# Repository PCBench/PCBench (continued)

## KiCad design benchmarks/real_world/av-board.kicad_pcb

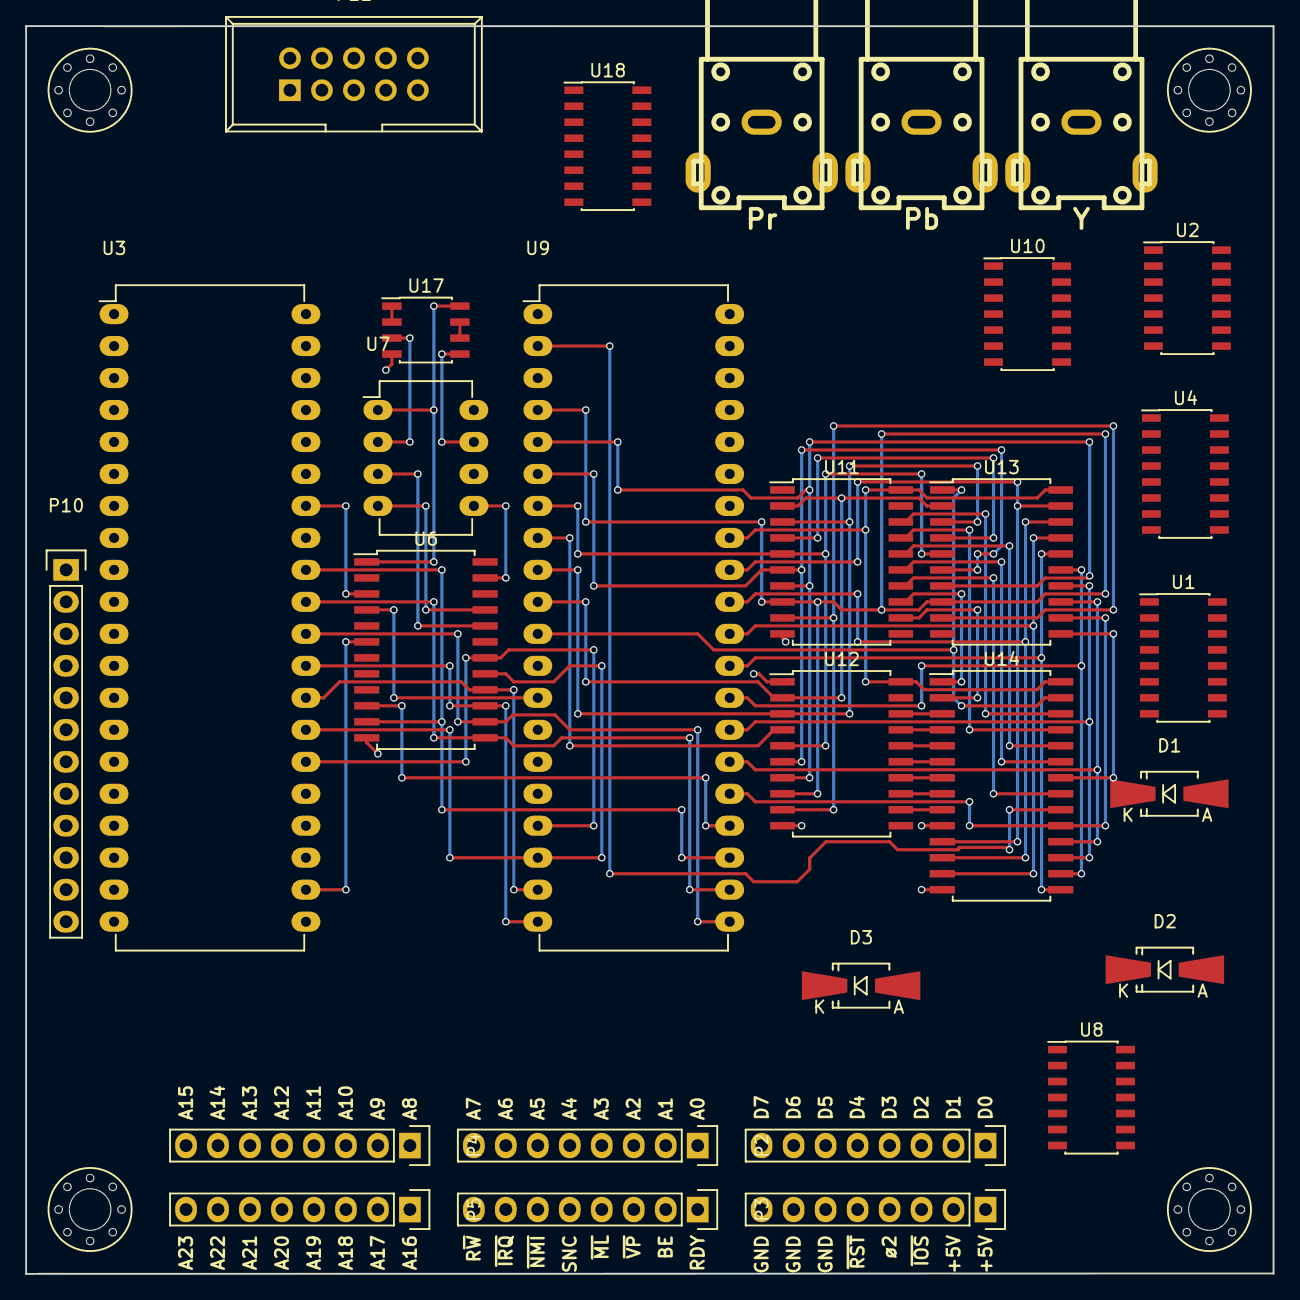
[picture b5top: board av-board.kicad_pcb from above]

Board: 2 copper layers, 99.1 x 99.1 mm, 33 parts (0 on the bottom side), 92 nets.

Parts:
D1, D2, D3: D_Small; SMA-SMB_Universal_Handsoldering
P1: D0..D7; Pin_Header_Straight_1x08
P2: A0..A7; Pin_Header_Straight_1x08
P3: CTRL1; Pin_Header_Straight_1x08
P4: A8..A15; Pin_Header_Straight_1x08
P5: A16..A23; Pin_Header_Straight_1x08
P6: CTRL2; Pin_Header_Straight_1x08
P7: Pr; rca_black
P8: Y; rca_black
P9: Pb; rca_black
P10: PARALLEL; Pin_Header_Straight_1x12
P11: KEYBOARD; IDC_Header_Straight_10pins
U1, U4, U18: 74HC138; SOIC-16_3.9x9.9mm_Pitch1.27mm
U2, U10: 74HC00; SOIC-14_3.9x8.7mm_Pitch1.27mm
U3: WD65C22; DIP-40_W15.24mm_LongPads
U6: YM3812; SOIC-24W_7.5x15.4mm_Pitch1.27mm
U7: YM3014; DIP-8_W7.62mm_LongPads
U8: 74HC04; SOIC-14_3.9x8.7mm_Pitch1.27mm
U9: TMS9929; DIP-40_W15.24mm_LongPads
U11, U12, U13: 74LS574; SOIC-20W_7.5x12.8mm_Pitch1.27mm
U14: CY62256; SOIC-28W_7.5x17.9mm_Pitch1.27mm
U17: TL072; SOIC-8_3.9x4.9mm_Pitch1.27mm
W1, W2, W3, W4: MOUNTING; M3_MOUNT

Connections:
+5V: P6.1, P6.2, P10.1, P11.2, U1.6, U1.16, U2.14, U3.20, U3.24, U4.16, U6.1, U7.1, U8.14, U9.33, U10.14, U11.20, U12.20, U13.20, U14.28, U17.8, U18.6, U18.16
/A0: P2.1, U3.38, U6.4, U9.13
/A1: P2.2, U3.37
/A2: P2.3, U3.36, U4.1
/A3: P2.4, U3.35, U4.2
/A4: P2.5, U1.1, U4.3
/A5: P2.6, U1.2, U4.6
/A6: P2.7, U1.3, U2.1
/A7: P2.8, U1.5, U2.2
/D0: P1.1, U3.33, U6.10, U9.24
/D1: P1.2, U3.32, U6.11, U9.23
/D2: P1.3, U3.31, U6.13, U9.22
/D3: P1.4, U3.30, U6.14, U9.21
/D4: P1.5, U3.29, U6.15, U9.20
/D5: P1.6, U3.28, U6.16, U9.19
/D6: P1.7, U3.27, U6.17, U9.18
/D7: P1.8, U3.26, U6.18, U9.17
/PHI2: P6.4, U3.25
/R/~W: P3.8, U3.22, U6.6, U10.12
/SPICLK: P11.3, U3.2
/SPIMISO: P11.1, U3.9
/SPIMOSI: P11.4, U3.3
/Sound/OUT: U17.1, U17.2
/Video/COL: U8.8, U12.11
/Video/SEL: U10.1, U10.13
/Video/VD0: U9.32, U13.19, U14.11
/Video/VD1: U9.31, U13.18, U14.12
/Video/VD2: U9.30, U13.17, U14.13
/Video/VD3: U9.29, U13.16, U14.15
/Video/VD4: U9.28, U13.15, U14.16
/Video/VD5: U9.27, U13.14, U14.17
/Video/VD6: U9.26, U13.13, U14.18
/Video/VD7: U9.25, U13.12, U14.19
/Video/VR/~W: U9.11, U13.1, U14.27
/Video/WR: U13.11, U14.22
/Video/~CAS: U9.2, U14.20
/Video/~CSR: U9.15, U10.11
/Video/~CSW: U9.14, U10.3
/W/~R: U6.5, U10.2
/~IOPAGE: P6.3, U1.4, U4.4
/~IRQ: D1.2, D2.2, D3.2, P3.7
/~RST: P6.5, U3.34, U6.3, U9.34
/~SNDS: U4.14, U6.7
/~SPIIRQ2: P11.9, U3.39
GND: P6.6, P6.7, P6.8, P7.2, P8.2, P9.2, P10.12, P11.6, P11.8, P11.10, U1.8, U2.7, U3.1, U4.8, U6.12, U7.6, U8.7, U9.12, U10.7, U11.1, U11.10, U12.1, U12.10, U13.10, U14.10, U14.14, U17.4, U18.4, U18.5, U18.8
unnamed: U7.7, U17.5
unnamed: D1.1, U3.21
unnamed: D2.1, U6.2
unnamed: D3.1, U9.16
unnamed: P10.2, U3.10
unnamed: P10.3, U3.11
unnamed: P10.4, U3.12
unnamed: P10.5, U3.13
unnamed: P10.6, U3.14
unnamed: P10.7, U3.15
unnamed: P10.8, U3.16
unnamed: P10.9, U3.17
unnamed: P10.10, U3.18
unnamed: P10.11, U3.19
unnamed: U1.15, U3.23
unnamed: U2.3, U4.5
unnamed: U6.20, U7.3
unnamed: U6.21, U7.4
unnamed: U6.23, U7.5
unnamed: U8.9, U8.10
unnamed: U9.10, U11.2, U12.2, U13.2
unnamed: U9.9, U11.3, U12.3, U13.3
unnamed: U9.8, U11.4, U12.4, U13.4
unnamed: U9.7, U11.5, U12.5, U13.5
unnamed: U9.6, U11.6, U12.6, U13.6
unnamed: U9.5, U11.7, U12.7, U13.7
unnamed: U9.4, U11.8, U12.8, U13.8
unnamed: U9.3, U11.9, U12.9, U13.9
unnamed: U11.12, U14.2
unnamed: U11.13, U14.1
unnamed: U11.14, U14.21
unnamed: U11.15, U14.23
unnamed: U11.16, U14.24
unnamed: U11.17, U14.25
unnamed: U11.18, U14.26
unnamed: U12.12, U14.9
unnamed: U12.13, U14.8
unnamed: U12.14, U14.7
unnamed: U12.15, U14.6
unnamed: U12.16, U14.5
unnamed: U12.17, U14.4
unnamed: U12.18, U14.3
unnamed: U7.2, U17.3
unnamed: U7.8, U17.6, U17.7
unnamed: U3.4, U18.1
unnamed: U3.5, U18.2
unnamed: U3.6, U18.3

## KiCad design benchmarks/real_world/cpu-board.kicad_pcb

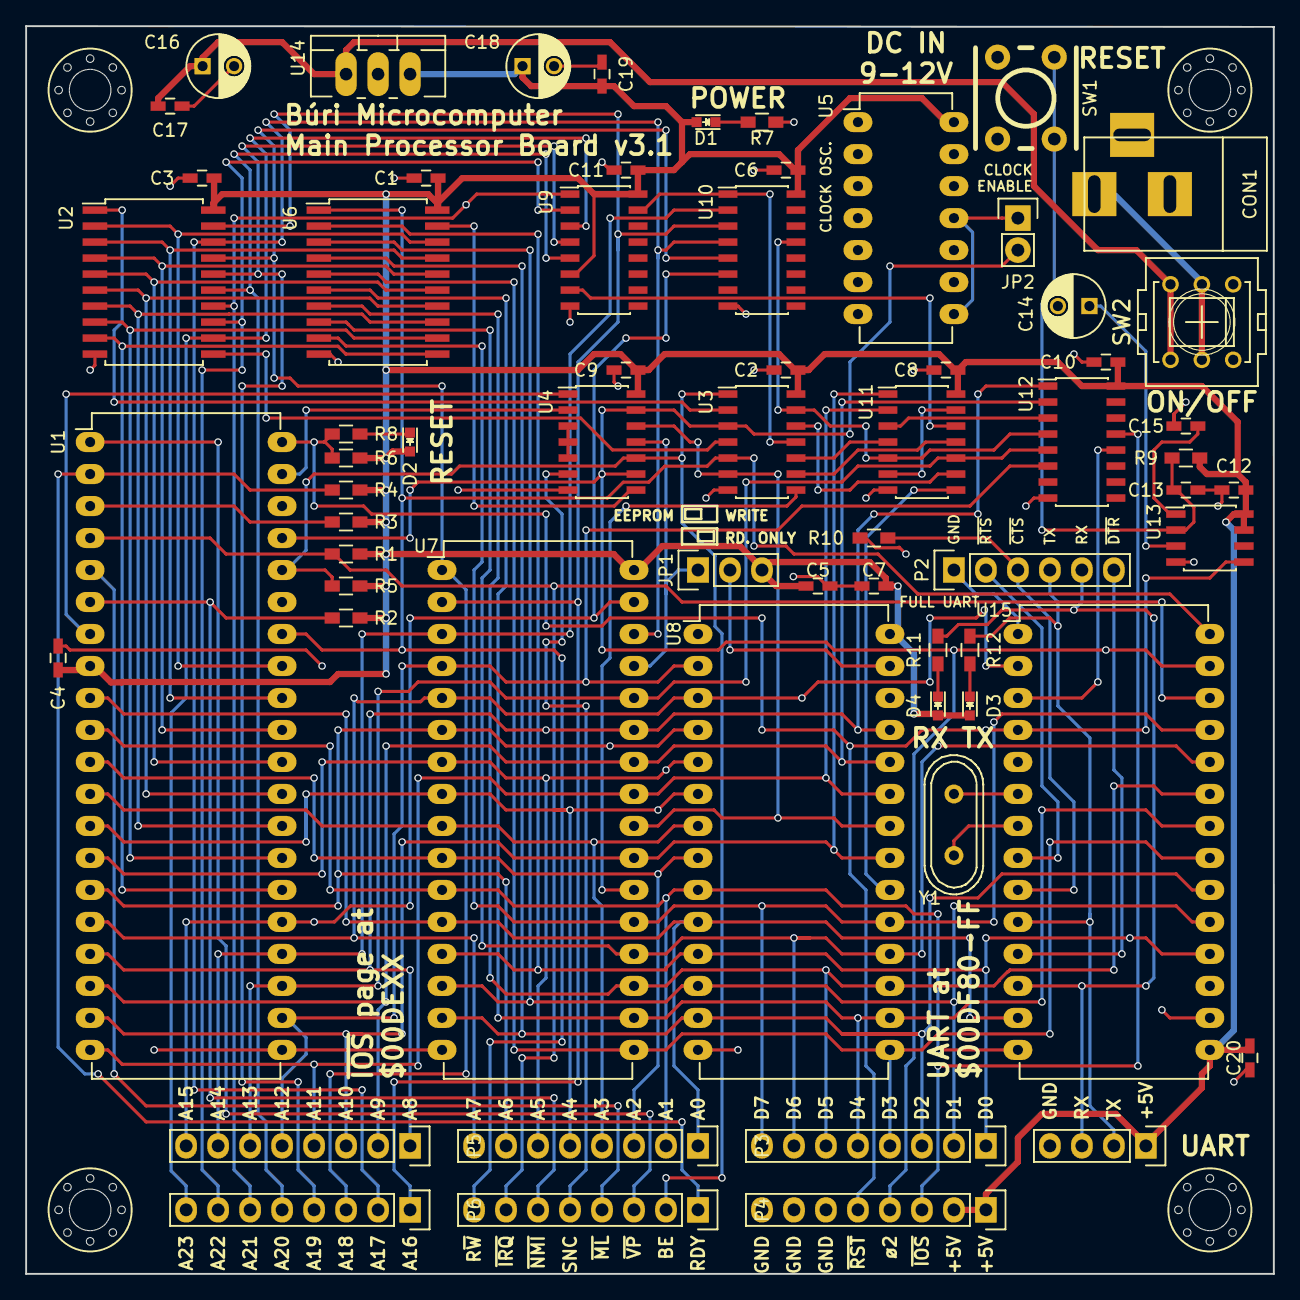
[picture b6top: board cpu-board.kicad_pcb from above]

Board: 2 copper layers, 99.1 x 99.1 mm, 69 parts (0 on the bottom side), 91 nets.

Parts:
C1, C2, C3, C4, C5, C6, C7, C8, C9, C10, C11, C12, C13, C15, C17, C19, C20: 100n; C_0603_HandSoldering
C14, C16, C18: 1µ; C_Radial_D5_L6_P2.5
CON1: POWER_IN; BARREL_JACK
D1: PWR; LED_0603
D2: RST; LED_0603
D3: TX; LED_0603
D4: RX; LED_0603
JP1: ROMWRITE; Pin_Header_Straight_1x03
JP2: Jumper_NC_Small; Pin_Header_Straight_1x02
P1: D0..D7; Pin_Header_Straight_1x08
P2: UART; Pin_Header_Straight_1x06
P3: A0..A7; Pin_Header_Straight_1x08
P4: CTRL1; Pin_Header_Straight_1x08
P5: A8..A15; Pin_Header_Straight_1x08
P6: A16..A23; Pin_Header_Straight_1x08
P7: CTRL2; Pin_Header_Straight_1x08
P8: UARTMINI; Pin_Header_Straight_1x04
R1, R2, R3, R4, R5, R6, R7, R8, R9, R10, R11, R12: 330; R_0603_HandSoldering
SW1: RESET; SW_M6_PTH
SW2: ON/OFF; switch-misc-PVA2R
U1: W65C816; DIP-40_W15.24mm_LongPads
U2: 74HC573; SOIC-20_7.5x12.8mm_Pitch1.27mm
U3: 74HC04; SOIC-14_3.9x8.7mm_Pitch1.27mm
U4, U11: 74HC00; SOIC-14_3.9x8.7mm_Pitch1.27mm
U5: CLOCK; DIP-14_W7.62mm_LongPads
U6: 74HC245; SOIC-20_7.5x12.8mm_Pitch1.27mm
U7: AS6C4008; DIP-32_W15.24mm_LongPads
U8: AT28C64B; DIP-28_W15.24mm_LongPads
U9, U10, U12: 74HC138; SOIC-16_3.9x9.9mm_Pitch1.27mm
U13: TL7705A; SOIC-8_3.9x4.9mm_Pitch1.27mm
U14: 7805; TO-220_Neutral123_Vertical_LargePads
U15: W65C51; DIP-28_W15.24mm_LongPads
W1, W2, W3, W4: MOUNTING; M3_MOUNT
Y1: 1.8432M; Crystal_HC49-U_Vertical

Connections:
+5V: C1.1, C2.1, C3.1, C4.1, C5.1, C6.1, C7.1, C8.1, C9.1, C10.1, C11.1, C12.1, C18.1, C19.1, C20.1, D1.2, D2.2, D3.2, D4.2, JP1.3, P7.1, P7.2, P8.1, R1.1, R2.1, R3.1, R4.1, R5.1, R6.1, R9.1, U1.8, U2.20, U3.14, U4.14, U5.14, U6.20, U7.32, U8.28, U9.6, U9.16, U10.16, U11.14, U12.16, U13.7, U13.8, U14.3, U15.15
/A2: P3.3, U1.11, U7.10, U8.8
/A3: P3.4, U1.12, U7.9, U8.7
/A4: P3.5, U1.13, U7.8, U8.6
/A5: P3.6, U1.14, U7.7, U8.5
/A6: P3.7, U1.15, U7.6, U8.4
/ACIA/CS0: P3.8, U1.16, U7.5, U8.3, U15.2
/ACIA/D0: P1.1, U6.2, U7.13, U8.11, U15.18
/ACIA/D1: P1.2, U6.3, U7.14, U8.12, U15.19
/ACIA/D2: P1.3, U6.4, U7.15, U8.13, U15.20
/ACIA/D3: P1.4, U6.5, U7.17, U8.15, U15.21
/ACIA/D4: P1.5, U6.6, U7.18, U8.16, U15.22
/ACIA/D5: P1.6, U6.7, U7.19, U8.17, U15.23
/ACIA/D6: P1.7, U6.8, U7.20, U8.18, U15.24
/ACIA/D7: P1.8, U6.9, U7.21, U8.19, U15.25
/ACIA/PHI2: JP2.2, P7.4, U1.37, U3.3, U4.9, U4.13, U15.27
/ACIA/R/~W: P4.8, U1.34, U3.5, U6.1, U15.28
/ACIA/RS0: P3.1, U1.9, U7.12, U8.10, U15.13
/ACIA/RS1: P3.2, U1.10, U7.11, U8.9, U15.14
/ACIA/RX: P2.5, P8.3, R12.2, U15.12
/ACIA/TX: P2.4, P8.2, R11.2, U15.10
/ACIA/~CS1: U12.12, U15.3
/ACIA/~CTS: P2.3, R10.1, U15.9
/ACIA/~DTR: P2.6, U15.11
/ACIA/~IRQ: P4.7, R1.2, U1.4, U15.26
/ACIA/~RTS: P2.2, U15.8
/Address decode/A8: P5.1, U1.17, U7.27, U8.25, U12.1
/Address decode/A9: P5.2, U1.18, U7.26, U8.24, U12.2
/Address decode/A10: P5.3, U1.19, U7.23, U8.21, U11.1
/Address decode/A11: P5.4, U1.20, U7.25, U8.23, U11.2
/Address decode/A12: P5.5, U1.22, U7.4, U8.2, U12.6
/Address decode/A13: P5.6, U1.23, U7.28, U11.10, U12.5
/Address decode/A14: P5.7, U1.24, U7.3, U10.2
/Address decode/A15: P5.8, U1.25, U7.31, U10.6
/Address decode/A16: P6.1, U2.19, U7.2, U10.3
/Address decode/A17: P6.2, U2.18, U7.30, U10.4
/Address decode/A18: P6.3, U2.17, U7.1, U10.5
/Address decode/A19: P6.4, U2.16, U9.4
/Address decode/A20: P6.5, U2.15, U9.5
/Address decode/A21: P6.6, U2.14, U9.1
/Address decode/A22: P6.7, U2.13, U9.2
/Address decode/A23: P6.8, U2.12, U9.3
/Address decode/LOADDR: U3.10, U11.4
/Address decode/RAMHOLE: U3.12, U11.9
/Address decode/RAMSEL: U3.9, U11.11
/Address decode/~HIADDR: U9.7, U11.12
/Address decode/~IO2: P7.3, U12.13
/Address decode/~LOADDR: U3.11, U9.15, U10.1
/Address decode/~LORAM: U11.6, U11.13
/Address decode/~RAMHOLE: U3.13, U10.13, U11.5, U12.4
/Address decode/~ROMSEL: U8.20, U11.8
/BA0: U1.33, U2.2, U6.18
/BA1: U1.32, U2.3, U6.17
/BA2: U1.31, U2.4, U6.16
/BA3: U1.30, U2.5, U6.15
/BA4: U1.29, U2.6, U6.14
/BA5: U1.28, U2.7, U6.13
/BA6: U1.27, U2.8, U6.12
/BA7: U1.26, U2.9, U6.11
/BE: P4.2, R5.2, U1.36, U3.1, U4.10
/RDY: P4.1, R4.2, U1.2
/Reset & power/~RESET: P7.5, R6.2, R8.2, U1.40, U13.5, U15.4
/SYNC: P4.5, U4.6
/VDA: U1.39, U4.2
/VPA: U1.7, U4.1
/~ABORT: R3.2, U1.3
/~MEMWE: JP1.1, U4.11, U7.29
/~ML: P4.4, U1.5
/~NMI: P4.6, R2.2, U1.6
/~RAMSEL: U3.8, U7.22
/~ROMWE: JP1.2, U8.27
/~R~/W: U3.6, U4.12, U7.24, U8.22
/~VP: P4.3, U1.1
GND: C1.2, C2.2, C3.2, C4.2, C5.2, C6.2, C7.2, C8.2, C9.2, C10.2, C11.2, C12.2, C13.2, C14.2, C15.2, C16.2, C17.2, C18.2, C19.2, C20.2, CON1.2, P2.1, P7.6, P7.7, P7.8, P8.4, R7.1, R10.2, SW1.1, U1.21, U2.10, U3.7, U4.7, U5.4, U5.7, U6.10, U7.16, U8.14, U9.8, U10.8, U11.7, U12.8, U13.4, U14.2, U15.1, U15.16, U15.17
unnamed: C13.1, R9.2, SW1.2, U13.2
unnamed: C14.1, U13.3
unnamed: C15.1, U13.1
unnamed: C16.1, C17.1, SW2.1, SW2.4, U14.1
unnamed: CON1.1, SW2.2, SW2.5
unnamed: D1.1, R7.2
unnamed: D2.1, R8.1
unnamed: D3.1, R11.1
unnamed: D4.1, R12.1
unnamed: JP2.1, U5.8, U5.11
unnamed: U2.1, U3.2
unnamed: U2.11, U3.4
unnamed: U4.3, U4.4, U4.5
unnamed: U4.8, U6.19
unnamed: U11.3, U12.3
unnamed: U15.6, Y1.1
unnamed: U15.7, Y1.2

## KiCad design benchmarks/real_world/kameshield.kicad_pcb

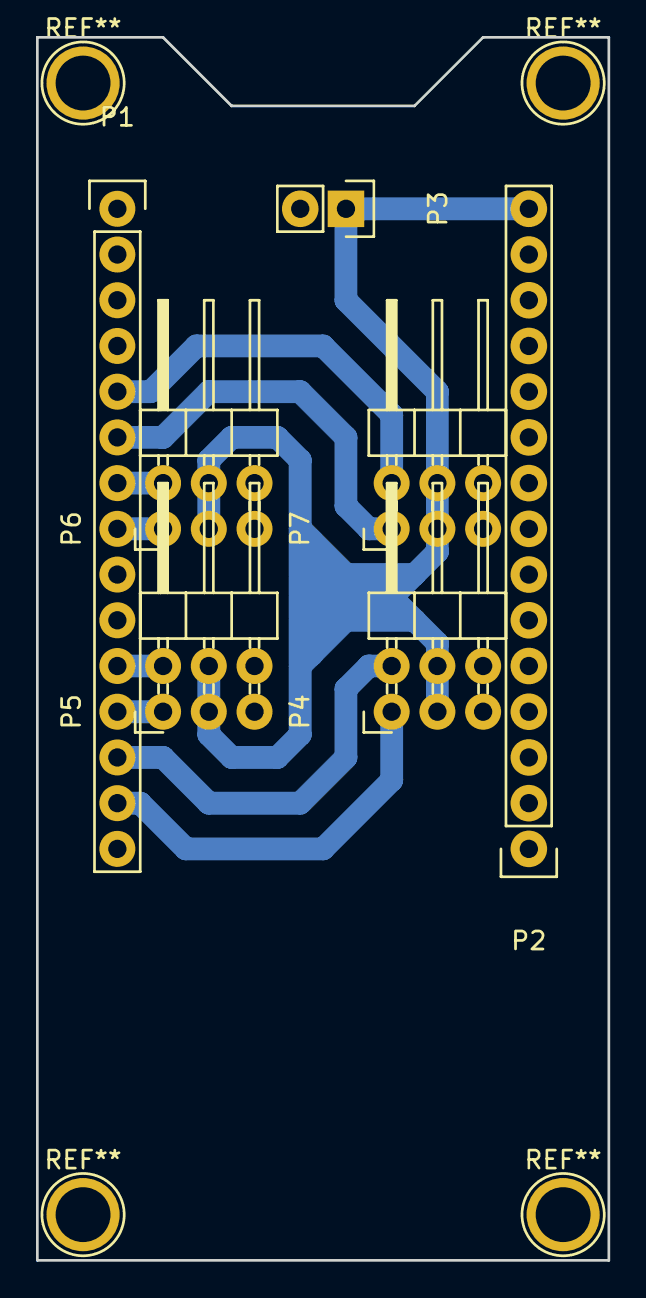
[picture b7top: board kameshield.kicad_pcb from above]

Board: 2 copper layers, 31.8 x 67.9 mm, 7 parts (0 on the bottom side), 10 nets.

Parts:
P1, P2: CONN_01X15; Pin_Header_Straight_1x15
P3: CONN_01X02; Pin_Header_Straight_1x02
P4, P5, P6, P7: CONN_02X03; Pin_Header_Angled_2x03

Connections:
D1: P1.14, P4.1
D2: P1.13, P4.2
D3: P1.12, P5.1
D4: P1.11, P5.2
D5: P1.8, P6.1
D6: P1.7, P6.2
D7: P1.6, P7.1
D8: P1.5, P7.2
GND: P1.2, P1.9, P2.10, P2.14, P3.2, P4.5, P4.6, P5.5, P5.6, P6.5, P6.6, P7.5, P7.6
V+: P2.15, P3.1, P4.3, P4.4, P5.3, P5.4, P6.3, P6.4, P7.3, P7.4

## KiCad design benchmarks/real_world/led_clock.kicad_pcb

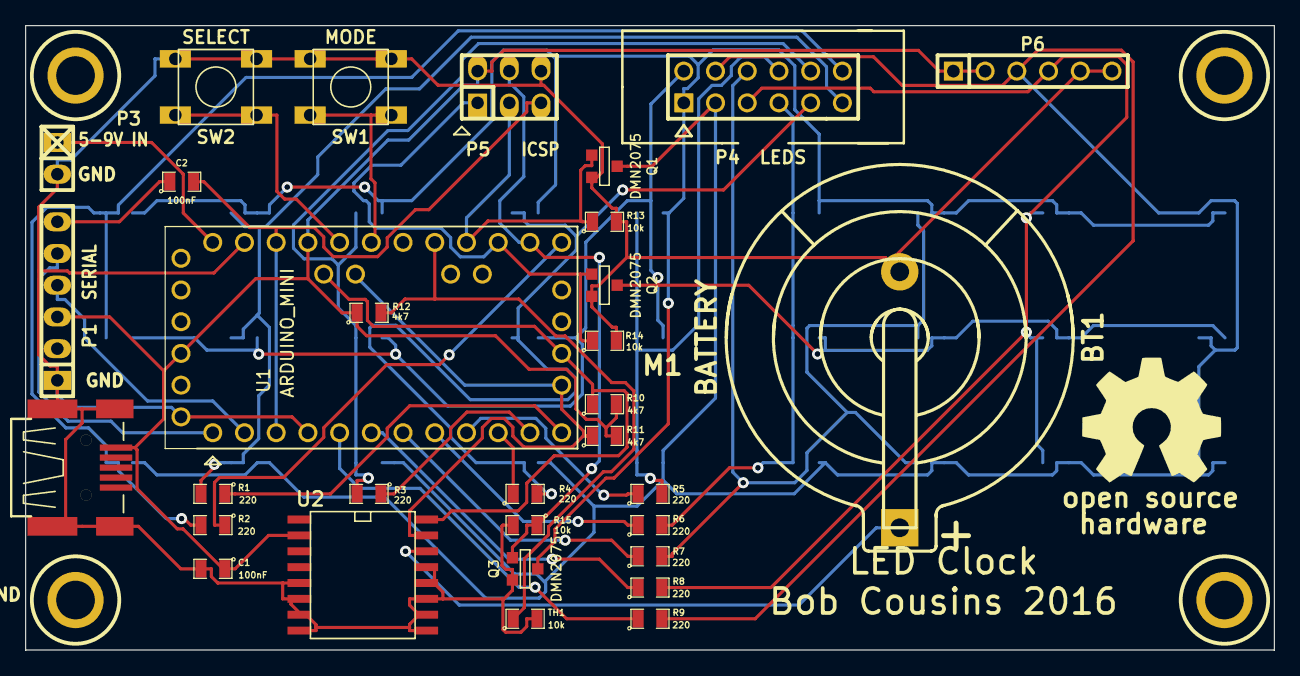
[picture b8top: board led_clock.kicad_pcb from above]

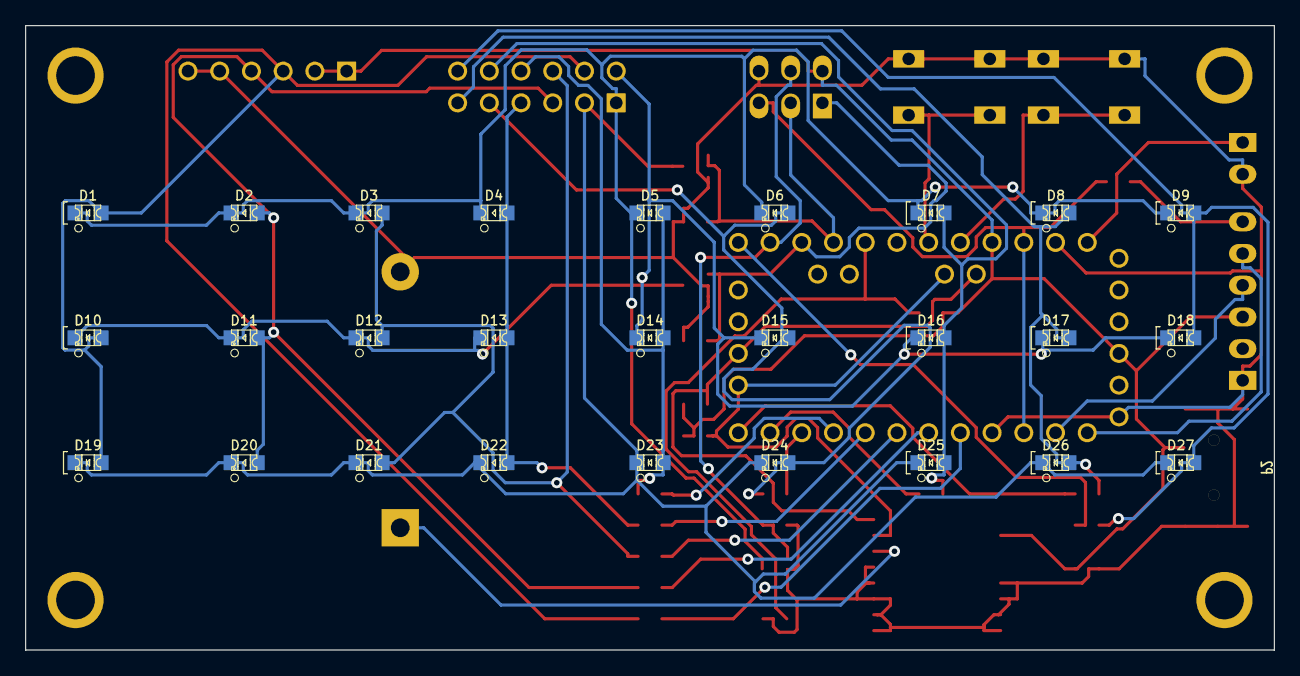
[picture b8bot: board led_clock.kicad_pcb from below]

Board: 2 copper layers, 100.0 x 50.0 mm, 65 parts (27 on the bottom side), 37 nets.

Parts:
BT1: BATTERY; keystone_106
C1, C2: 100nF; SM0805
D1, D7, D8, D9, D10, D16, D17, D18, D19, D25, D26, D27: LED; LED-0805_RED
D2, D3, D4, D11, D12, D13, D20, D21, D22: LED; LED-0805_GREEN
D5, D6, D14, D15, D23, D24: LED; LED-0805_BLUE
H1, H2, H3, H4: HOLE_RMC; HOLE_M3
M1: PCB_GREEN_RMC
M2: LOGO_OSHW; OSHW_logo_2
P1: SERIAL; pin_strip_6
P2: CONN_5; CONN_MiniAB_SMT_RMC
P3: 5-9V IN; pin_strip_2
P4: LEDS; PIN_ARRAY_6x2_RMC
P5: ICSP; pin_strip_3x2
P6: CONN_6; PIN_ARRAY-6X1
Q1, Q2, Q3: DMN2075; SOT23GDS
R1, R2, R3, R4, R5, R6, R7, R8, R9: 220; SM0805
R10, R11, R12: 4k7; SM0805
R13, R14, R15: 10k; SM0805
SW1: MODE; SW_6x6_MULTI
SW2: SELECT; SW_6x6_MULTI
TH1: 10k; SM0805
U1: ARDUINO_MINI
U2: DS3231N; SO16L

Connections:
+5V: C1.1, P1.3, P2.1, P5.2, P6.1, P6.2, R10.2, R11.2, R12.1, U1.+5V, U2.2
/MISO: P5.1, Q2.G, R14.1, U1.12
/MOSI: P5.4, Q3.G, R15.1, U1.11
/SCK: P5.3, Q1.G, R13.1, U1.13
/SCL: R10.1, U1.A5, U2.16
/SDA: R11.1, U1.A4, U2.15
/SW1: SW1.1, U1.A2
/SW2: SW2.1, U1.A3
/VIN: P3.1, U1.VIN
/~RST: C2.2, P5.5, U1.RST
COL1: D1.1, D10.1, D19.1, P4.4, P6.3, R9.2
COL2: D2.1, D11.1, D20.1, P4.5, P6.4, R8.2
COL3: D3.1, D12.1, D21.1, P4.6, R7.2
COL4: D4.1, D13.1, D22.1, P4.7, R6.2
COL5: D5.1, D14.1, D23.1, P4.8, R5.2
COL6: D6.1, D15.1, D24.1, P4.9, R4.2
COL7: D7.1, D16.1, D25.1, P4.10, R3.2
COL8: D8.1, D17.1, D26.1, P4.11, R2.2
COL9: D9.1, D18.1, D27.1, P4.12, R1.2
GND: BT1.2, C1.2, P1.1, P2.5, P3.2, P5.6, P6.5, P6.6, Q1.S, Q2.S, Q3.S, R13.2, R14.2, R15.2, SW1.2, SW2.2, TH1.2, U1.GND, U2.5, U2.6, U2.7, U2.8, U2.9, U2.10, U2.11, U2.12, U2.13
unnamed: R5.1, U1.6
unnamed: R6.1, U1.5
unnamed: R7.1, U1.4
unnamed: R8.1, U1.3
unnamed: R9.1, U1.2
unnamed: R4.1, U1.7
unnamed: C2.1, P1.6
unnamed: R1.1, U1.10
unnamed: R2.1, U1.9
unnamed: R3.1, U1.8
unnamed: R12.2, TH1.1, U1.A0
unnamed: BT1.1, U2.14
ROW1: D1.2, D2.2, D3.2, D4.2, D5.2, D6.2, D7.2, D8.2, D9.2, P4.1, Q3.D
ROW2: D10.2, D11.2, D12.2, D13.2, D14.2, D15.2, D16.2, D17.2, D18.2, P4.2, Q2.D
ROW3: D19.2, D20.2, D21.2, D22.2, D23.2, D24.2, D25.2, D26.2, D27.2, P4.3, Q1.D
RX: P1.4, U1.0
TX: P1.5, U1.1
